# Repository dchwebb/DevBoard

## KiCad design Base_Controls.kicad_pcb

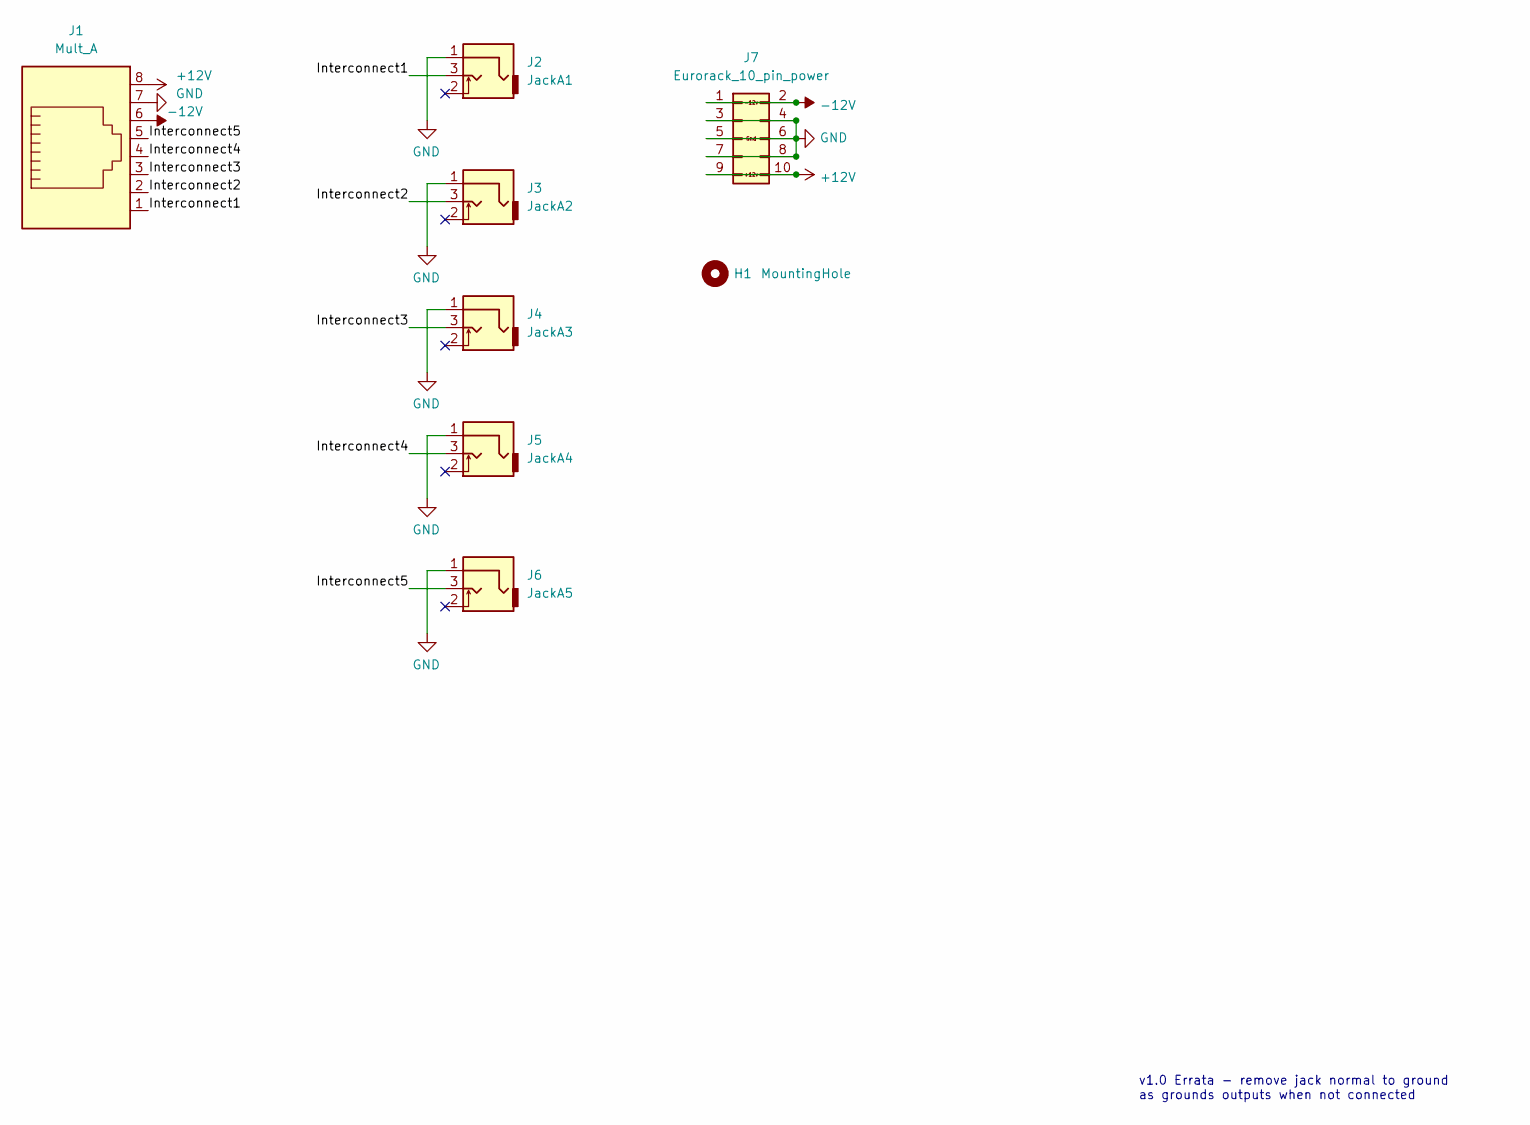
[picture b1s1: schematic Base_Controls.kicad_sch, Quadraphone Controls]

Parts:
H1: MountingHole; MountingHole_3.2mm_M3_ISO14580
J1: Mult_A; RJ45_Molex_42878-8506
J2: JackA1; THONKICONN_hole
J3: JackA2; THONKICONN_hole
J4: JackA3; THONKICONN_hole
J5: JackA4; THONKICONN_hole
J6: JackA5; THONKICONN_hole
J7: Eurorack_10_pin_power; PinHeader_2x05_P2.54mm_Vertical

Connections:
+12V: J1.8, J7.9, J7.10
-12V: J1.6, J7.1, J7.2
/Interconnect1: J1.1, J2.3
/Interconnect2: J1.2, J3.3
/Interconnect3: J1.3, J4.3
/Interconnect4: J1.4, J5.3
/Interconnect5: J1.5, J6.3
GND: J1.7, J2.1, J3.1, J4.1, J5.1, J6.1, J7.3, J7.4, J7.5, J7.6, J7.7, J7.8

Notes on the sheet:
v1.0 Errata - remove jack normal to ground as grounds outputs when not connected

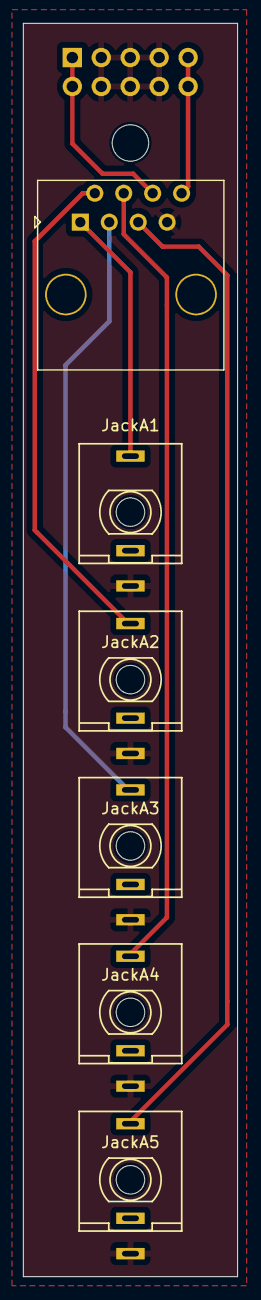
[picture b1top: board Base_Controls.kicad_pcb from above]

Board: 2 copper layers, 18.8 x 110.0 mm, 8 parts (1 on the bottom side), 8 nets.

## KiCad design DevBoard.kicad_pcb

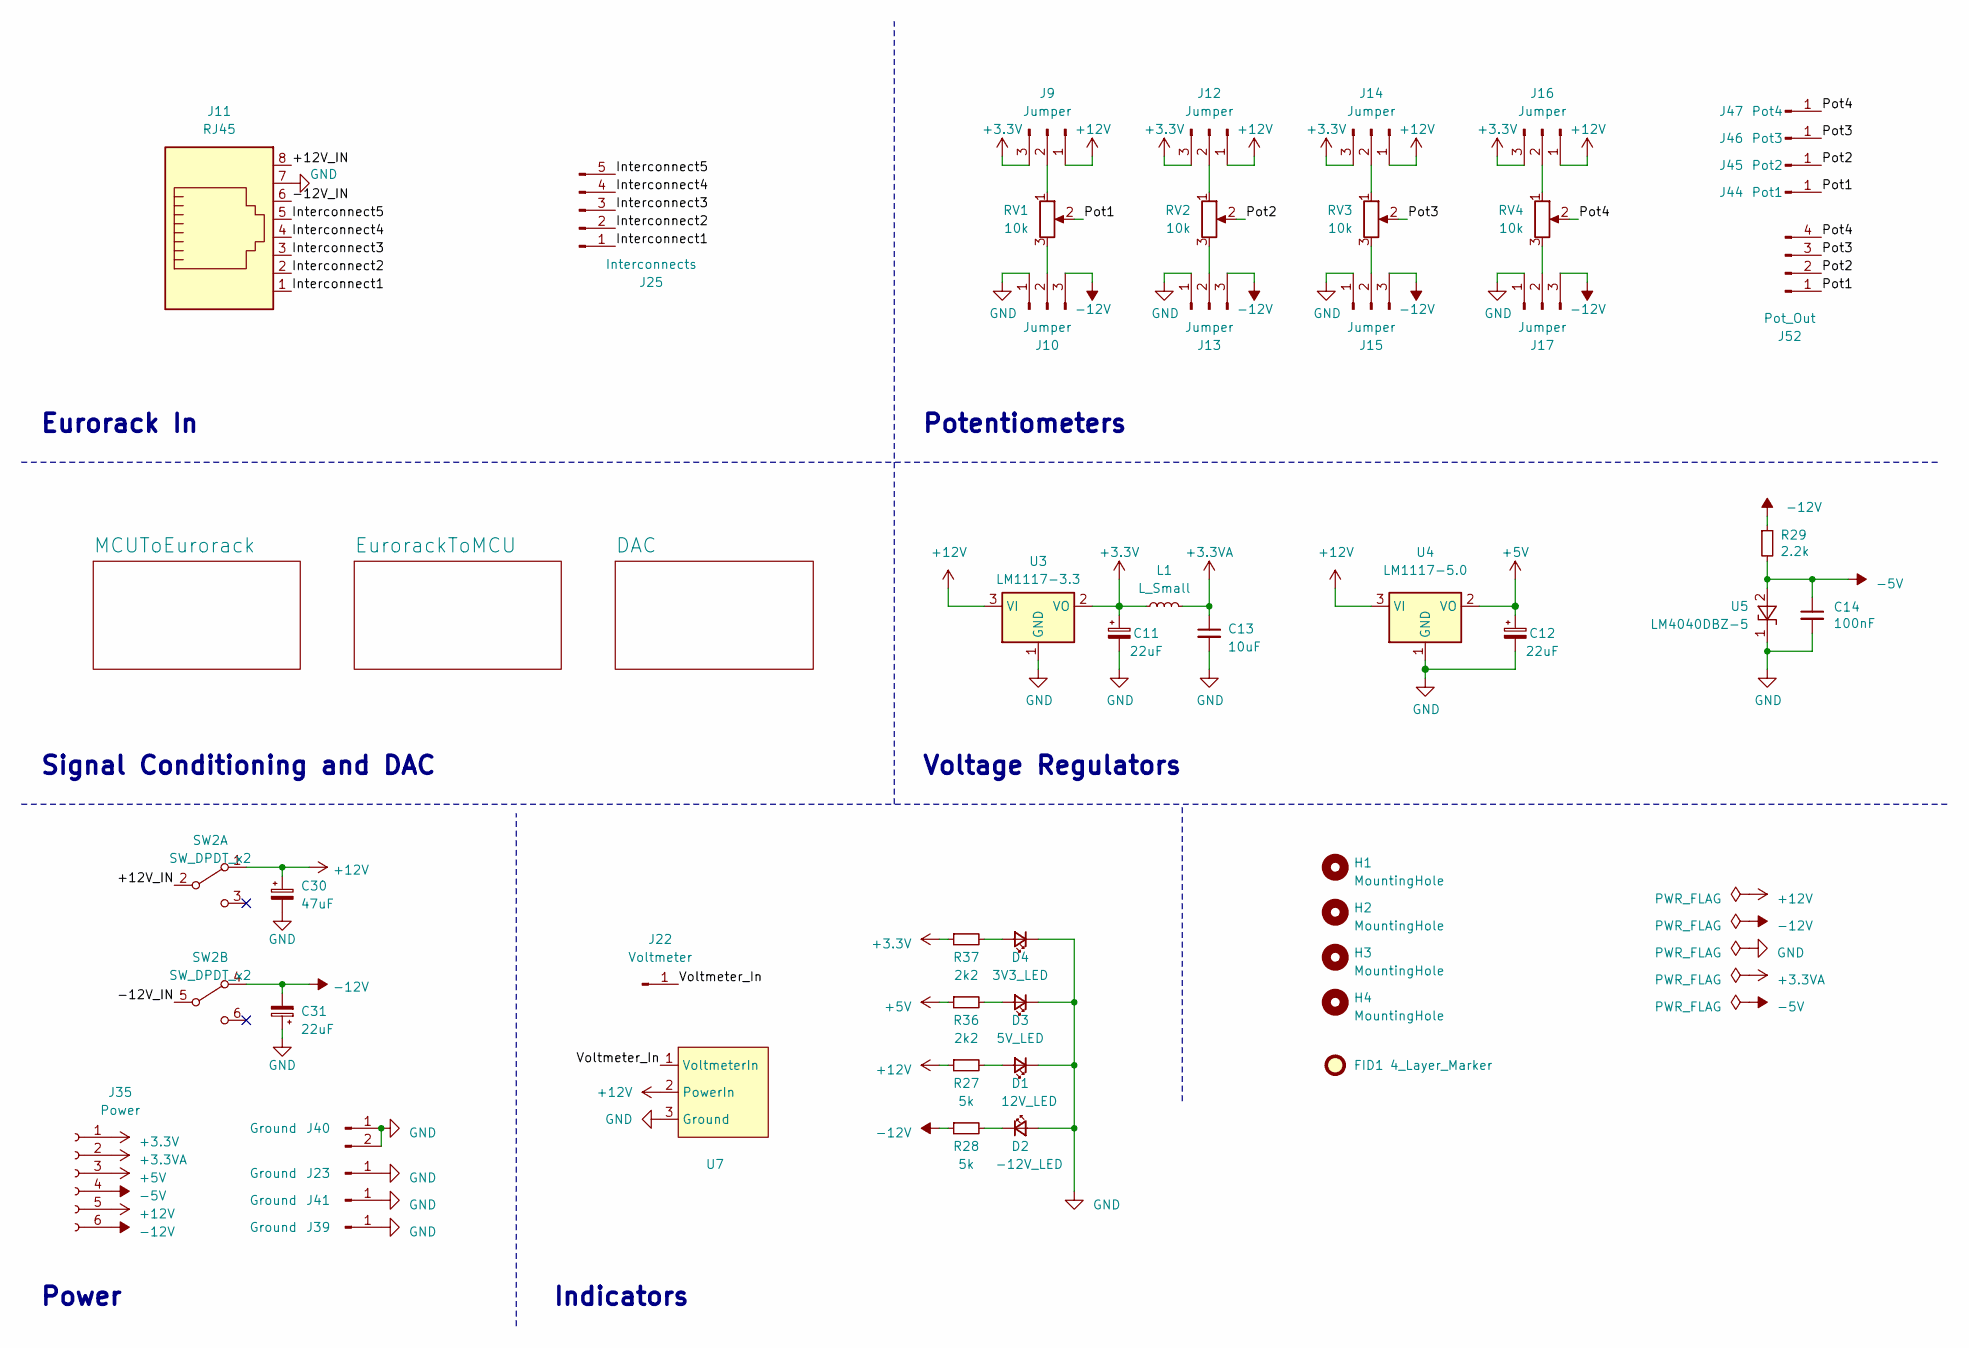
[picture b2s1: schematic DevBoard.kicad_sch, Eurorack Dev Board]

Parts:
C11, C12, C31: 22uF; CP_Elec_4x5.8
C13: 10uF; C_0805_2012Metric
C14: 100nF; C_0805_2012Metric
C30: 47uF; CP_Elec_5x5.4
D1: 12V_LED; LED_0603_1608Metric
D2: -12V_LED; LED_0603_1608Metric
D3: 5V_LED; LED_0603_1608Metric
D4: 3V3_LED; LED_0603_1608Metric
FID1: 4_Layer_Marker; 4_Layer_Markers
H1, H2, H3, H4: MountingHole; MountingHole_3.2mm_M3
J9, J10, J12, J13, J14, J15, J16, J17: Jumper; PinHeader_1x03_P2.54mm_Vertical
J11: RJ45; RJ45_Amphenol_Style
J22: Voltmeter; PinSocket_1x01_P2.54mm_Vertical
J23, J39, J41: Ground; PinHeader_1x01_P2.54mm_Vertical
J25: Interconnects; PinSocket_1x05_P2.54mm_Vertical
J35: Power; PinSocket_1x06_P2.54mm_Vertical
J40: Ground; PinSocket_1x02_P2.54mm_Vertical
J44: Pot1; PinHeader_1x01_P2.54mm_Vertical
J45: Pot2; PinHeader_1x01_P2.54mm_Vertical
J46: Pot3; PinHeader_1x01_P2.54mm_Vertical
J47: Pot4; PinHeader_1x01_P2.54mm_Vertical
J52: Pot_Out; PinSocket_1x04_P2.54mm_Vertical
L1: L_Small; L_0805_2012Metric_Pad1.05x1.20mm_HandSolder; Part_Number C1046
R27, R28: 5k; R_0805_2012Metric
R29: 2.2k; R_0805_2012Metric
R36, R37: 2k2; R_0805_2012Metric
RV1, RV2, RV3, RV4: 10k; Alpha_9mm_Potentiometer_Aligned
SW2: SW_DPDT_x2; 100DP6T1B1M2QE_ON_ON_ON
U3: LM1117-3.3; SOT-223-3_TabPin2
U4: LM1117-5.0; SOT-223-3_TabPin2
U5: LM4040DBZ-5; SOT-23
U7: MiniVoltmeter

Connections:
+3.3V: C11.1, J9.3, J12.3, J14.3, J16.3, J35.1, L1.1, R37.1, U3.2 (VO); also elsewhere on the board
+3.3VA: C13.1, J35.2, L1.2; also elsewhere on the board
+5V: C12.1, J35.3, R36.1, U4.2 (VO)
+12V: C30.1, J9.1, J12.1, J14.1, J16.1, J35.5, R27.1, SW2.1 (A), U3.3 (VI), U4.3 (VI), U7.2 (PowerIn); also elsewhere on the board
-5V: C14.1, J35.4, R29.2, U5.2 (A); also elsewhere on the board
-12V: C31.2, J10.3, J13.3, J15.3, J17.3, J35.6, R28.1, R29.1, SW2.4 (A); also elsewhere on the board
/+12V_IN: J11.8, SW2.2 (B)
/-12V_IN: J11.6, SW2.5 (B)
/Interconnect1: J11.1, J25.1
/Interconnect2: J11.2, J25.2
/Interconnect3: J11.3, J25.3
/Interconnect4: J11.4, J25.4
/Interconnect5: J11.5, J25.5
/Pot1: J44.1, J52.1, RV1.2
/Pot2: J45.1, J52.2, RV2.2
/Pot3: J46.1, J52.3, RV3.2
/Pot4: J47.1, J52.4, RV4.2
/Voltmeter_In: J22.1, U7.1 (VoltmeterIn)
GND: C11.2, C12.2, C13.2, C14.2, C30.2, C31.1, D1.1 (K), D2.2 (A), D3.1 (K), D4.1 (K), J10.1, J11.7, J13.1, J15.1, J17.1, J23.1, J39.1, J40.1, J40.2, J41.1, U3.1 (GND), U4.1 (GND), U5.1 (K), U7.3 (Ground); also elsewhere on the board
unnamed: D1.2 (A), R27.2
unnamed: D2.1 (K), R28.2
unnamed: D3.2 (A), R36.2
unnamed: D4.2 (A), R37.2
unnamed: J9.2, RV1.1
unnamed: J10.2, RV1.3
unnamed: J12.2, RV2.1
unnamed: J13.2, RV2.3
unnamed: J14.2, RV3.1
unnamed: J15.2, RV3.3
unnamed: J16.2, RV4.1
unnamed: J17.2, RV4.3

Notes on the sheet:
Eurorack In
Potentiometers
Indicators
Power
Voltage Regulators
Signal Conditioning and DAC

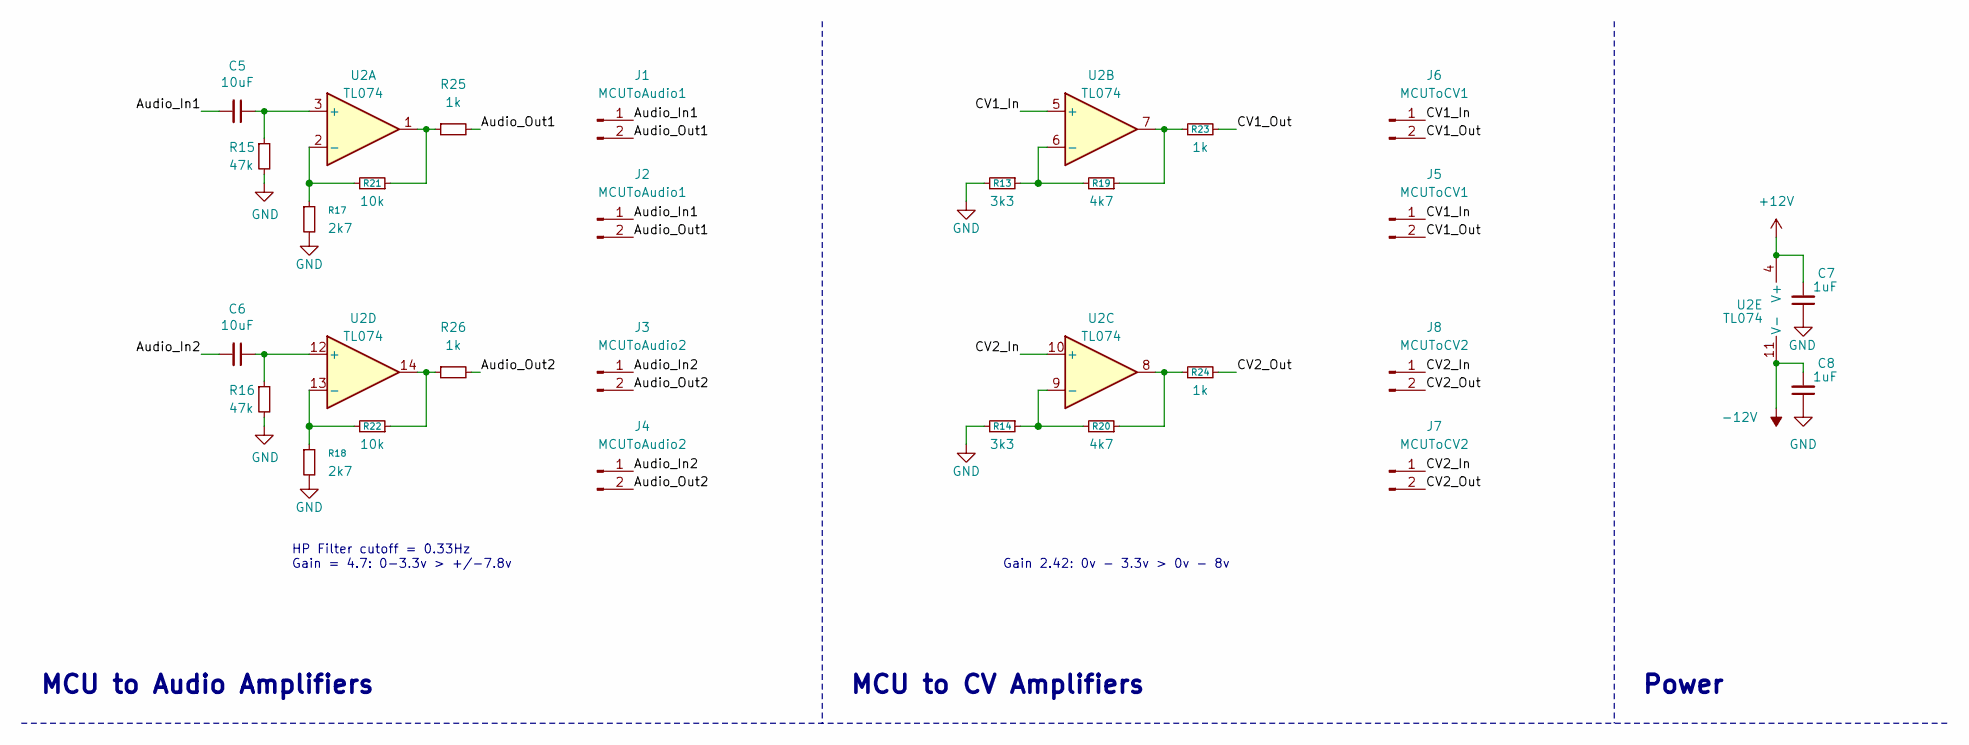
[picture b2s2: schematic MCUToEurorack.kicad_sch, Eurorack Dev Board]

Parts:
C5, C6: 10uF; C_0805_2012Metric
C7, C8: 1uF; C_0805_2012Metric
J1: MCUToAudio1; PinSocket_1x02_P2.54mm_Vertical
J2: MCUToAudio1; PinHeader_1x02_P2.54mm_Vertical
J3: MCUToAudio2; PinSocket_1x02_P2.54mm_Vertical
J4: MCUToAudio2; PinHeader_1x02_P2.54mm_Vertical
J5: MCUToCV1; PinHeader_1x02_P2.54mm_Vertical
J6: MCUToCV1; PinSocket_1x02_P2.54mm_Vertical
J7: MCUToCV2; PinHeader_1x02_P2.54mm_Vertical
J8: MCUToCV2; PinSocket_1x02_P2.54mm_Vertical
R13, R14: 3k3; R_0805_2012Metric; Part_Number C22978
R15, R16: 47k; R_0805_2012Metric
R17, R18: 2k7; R_0805_2012Metric; Part_Number C22978
R19, R20: 4k7; R_0805_2012Metric; Part_Number C23162
R21, R22: 10k; R_0805_2012Metric; Part_Number C23162
R23, R24: 1k; R_0805_2012Metric; Part_Number C21190
R25, R26: 1k; R_0805_2012Metric
U2: TL074; SOIC-14_3.9x8.7mm_P1.27mm

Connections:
+12V: C7.2, U2.4 (V+); also elsewhere on the board
-12V: C8.2, U2.11 (V-); also elsewhere on the board
/MCUToEurorack/Audio_In1: C5.2, J1.1, J2.1
/MCUToEurorack/Audio_In2: C6.2, J3.1, J4.1
/MCUToEurorack/Audio_Out1: J1.2, J2.2, R25.2
/MCUToEurorack/Audio_Out2: J3.2, J4.2, R26.2
/MCUToEurorack/CV1_In: J5.1, J6.1, U2.5 (+)
/MCUToEurorack/CV1_Out: J5.2, J6.2, R23.2
/MCUToEurorack/CV2_In: J7.1, J8.1, U2.10 (+)
/MCUToEurorack/CV2_Out: J7.2, J8.2, R24.2
GND: C7.1, C8.1, R13.2, R14.2, R15.2, R16.2, R17.2, R18.2; also elsewhere on the board
unnamed: R19.1, R23.1, U2.7
unnamed: R20.1, R24.1, U2.8
unnamed: R21.1, R25.1, U2.1
unnamed: R22.1, R26.1, U2.14
unnamed: C5.1, R15.1, U2.3 (+)
unnamed: R17.1, R21.2, U2.2 (-)
unnamed: R13.1, R19.2, U2.6 (-)
unnamed: R14.1, R20.2, U2.9 (-)
unnamed: C6.1, R16.1, U2.12 (+)
unnamed: R18.1, R22.2, U2.13 (-)

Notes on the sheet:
HP Filter cutoff = 0.33Hz Gain = 4.7: 0-3.3v > +/-7.8v
MCU to Audio Amplifiers
MCU to CV Amplifiers
Gain 2.42: 0v - 3.3v > 0v - 8v
Power

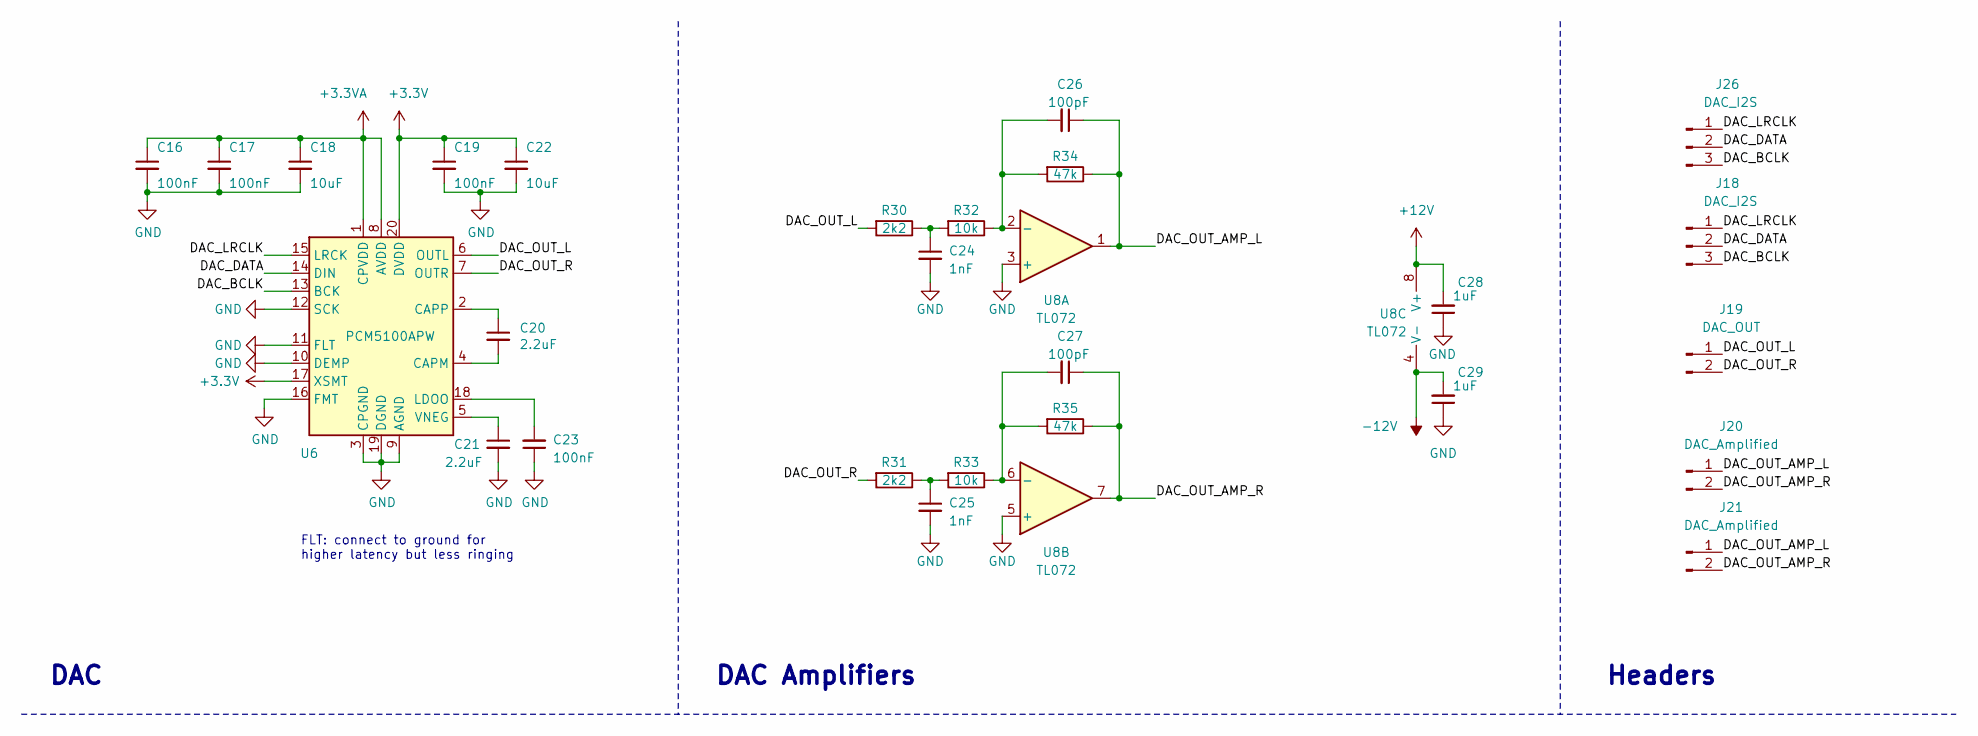
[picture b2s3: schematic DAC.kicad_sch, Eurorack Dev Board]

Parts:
C16, C17, C19, C23: 100nF; C_0805_2012Metric; Part_Number C14663
C18, C22: 10uF; C_0805_2012Metric; Part_Number C15850
C20, C21: 2.2uF; C_0805_2012Metric; Part_Number C23630
C24, C25: 1nF; C_0805_2012Metric; Part_Number C1588
C26, C27: 100pF; C_0805_2012Metric; Part_Number C14858
C28, C29: 1uF; C_0805_2012Metric
J18: DAC_I2S; PinHeader_1x03_P2.54mm_Vertical
J19: DAC_OUT; PinHeader_1x02_P2.54mm_Vertical
J20: DAC_Amplified; PinSocket_1x02_P2.54mm_Vertical
J21: DAC_Amplified; PinHeader_1x02_P2.54mm_Vertical
J26: DAC_I2S; PinSocket_1x03_P2.54mm_Vertical
R30, R31: 2k2; R_0805_2012Metric; Part_Number C4190
R32, R33: 10k; R_0805_2012Metric; Part_Number C25804
R34, R35: 47k; R_0805_2012Metric; Part_Number C25819
U6: PCM5100APW; TSSOP-20_4.4x6.5mm_P0.65mm; Part_Number C131154
U8: TL072; SOIC-8_3.9x4.9mm_P1.27mm; Part_Number C6961

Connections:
+3.3V: C19.1, C22.1, U6.17 (XSMT), U6.20 (DVDD); also elsewhere on the board
+3.3VA: C16.1, C17.1, C18.1, U6.1 (CPVDD), U6.8 (AVDD); also elsewhere on the board
+12V: C28.2, U8.8 (V+); also elsewhere on the board
-12V: C29.2, U8.4 (V-); also elsewhere on the board
/DAC/DAC_BCLK: J18.3, J26.3, U6.13 (BCK)
/DAC/DAC_DATA: J18.2, J26.2, U6.14 (DIN)
/DAC/DAC_LRCLK: J18.1, J26.1, U6.15 (LRCK)
/DAC/DAC_OUT_AMP_L: C26.1, J20.1, J21.1, R34.1, U8.1
/DAC/DAC_OUT_AMP_R: C27.1, J20.2, J21.2, R35.1, U8.7
/DAC/DAC_OUT_L: J19.1, R30.2, U6.6 (OUTL)
/DAC/DAC_OUT_R: J19.2, R31.2, U6.7 (OUTR)
GND: C16.2, C17.2, C18.2, C19.2, C21.2, C22.2, C23.1, C24.2, C25.2, C28.1, C29.1, U6.3 (CPGND), U6.9 (AGND), U6.10 (DEMP), U6.11 (FLT), U6.12 (SCK), U6.16 (FMT), U6.19 (DGND), U8.3 (+), U8.5 (+); also elsewhere on the board
unnamed: C24.1, R30.1, R32.2
unnamed: C25.1, R31.1, R33.2
unnamed: C20.2, U6.4 (CAPM)
unnamed: C20.1, U6.2 (CAPP)
unnamed: C23.2, U6.18 (LDOO)
unnamed: C21.1, U6.5 (VNEG)
unnamed: C26.2, R32.1, R34.2, U8.2 (-)
unnamed: C27.2, R33.1, R35.2, U8.6 (-)

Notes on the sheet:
Headers
DAC Amplifiers
DAC
FLT: connect to ground for higher latency but less ringing

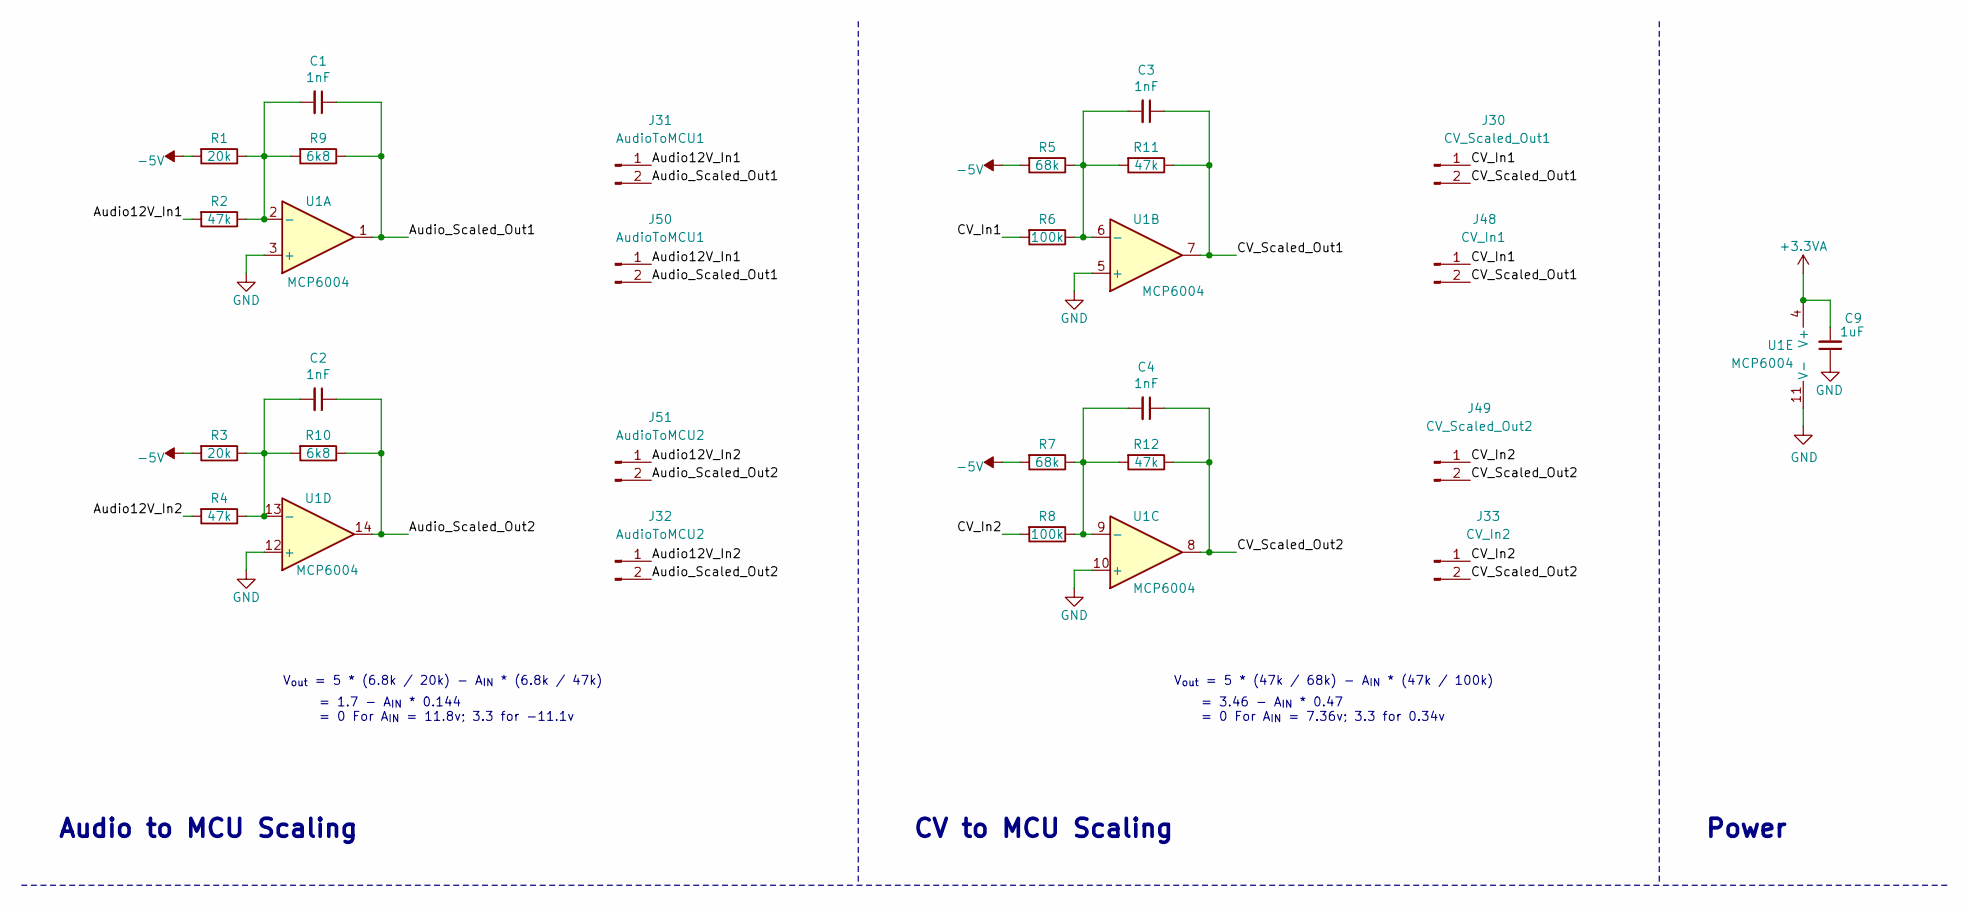
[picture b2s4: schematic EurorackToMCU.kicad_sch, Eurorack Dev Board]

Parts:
C1, C2, C3, C4: 1nF; C_0805_2012Metric; Part_Number C1595
C9: 1uF; C_0805_2012Metric
J30: CV_Scaled_Out1; PinSocket_1x02_P2.54mm_Vertical
J31: AudioToMCU1; PinSocket_1x02_P2.54mm_Vertical
J32: AudioToMCU2; PinHeader_1x02_P2.54mm_Vertical
J33: CV_In2; PinHeader_1x02_P2.54mm_Vertical
J48: CV_In1; PinHeader_1x02_P2.54mm_Vertical
J49: CV_Scaled_Out2; PinSocket_1x02_P2.54mm_Vertical
J50: AudioToMCU1; PinHeader_1x02_P2.54mm_Vertical
J51: AudioToMCU2; PinSocket_1x02_P2.54mm_Vertical
R1, R3: 20k; R_0805_2012Metric; Part_Number C4184
R2, R4, R11, R12: 47k; R_0805_2012Metric; Part_Number C25819
R5, R7: 68k; R_0805_2012Metric; Part_Number C23231
R6, R8: 100k; R_0805_2012Metric; Part_Number C25803
R9, R10: 6k8; R_0805_2012Metric; Part_Number C23212
U1: MCP6004; SOIC-14_3.9x8.7mm_P1.27mm; Part_Number C116668

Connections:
+3.3VA: C9.2, U1.4 (V+); also elsewhere on the board
-5V: R1.2, R3.2, R5.2, R7.2; also elsewhere on the board
/EurorackToMCU/Audio12V_In1: J31.1, J50.1, R2.2
/EurorackToMCU/Audio12V_In2: J32.1, J51.1, R4.2
/EurorackToMCU/Audio_Scaled_Out1: C1.1, J31.2, J50.2, R9.1, U1.1
/EurorackToMCU/Audio_Scaled_Out2: C2.1, J32.2, J51.2, R10.1, U1.14
/EurorackToMCU/CV_In1: J30.1, J48.1, R6.2
/EurorackToMCU/CV_In2: J33.1, J49.1, R8.2
/EurorackToMCU/CV_Scaled_Out1: C3.1, J30.2, J48.2, R11.1, U1.7
/EurorackToMCU/CV_Scaled_Out2: C4.1, J33.2, J49.2, R12.1, U1.8
GND: C9.1, U1.3 (+), U1.5 (+), U1.10 (+), U1.11 (V-), U1.12 (+); also elsewhere on the board
unnamed: C1.2, R1.1, R2.1, R9.2, U1.2 (-)
unnamed: C3.2, R5.1, R6.1, R11.2, U1.6 (-)
unnamed: C4.2, R7.1, R8.1, R12.2, U1.9 (-)
unnamed: C2.2, R3.1, R4.1, R10.2, U1.13 (-)

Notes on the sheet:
Power
Audio to MCU Scaling
CV to MCU Scaling
V_{out} = 5 * (6.8k / 20k) - A_{IN} * (6.8k / 47k)
V_{out} = 5 * (47k / 68k) - A_{IN} * (47k / 100k)
= 3.46 - A_{IN} * 0.47 = 0 For A_{IN} = 7.36v; 3.3 for 0.34v
= 1.7 - A_{IN} * 0.144 = 0 For A_{IN} = 11.8v; 3.3 for -11.1v

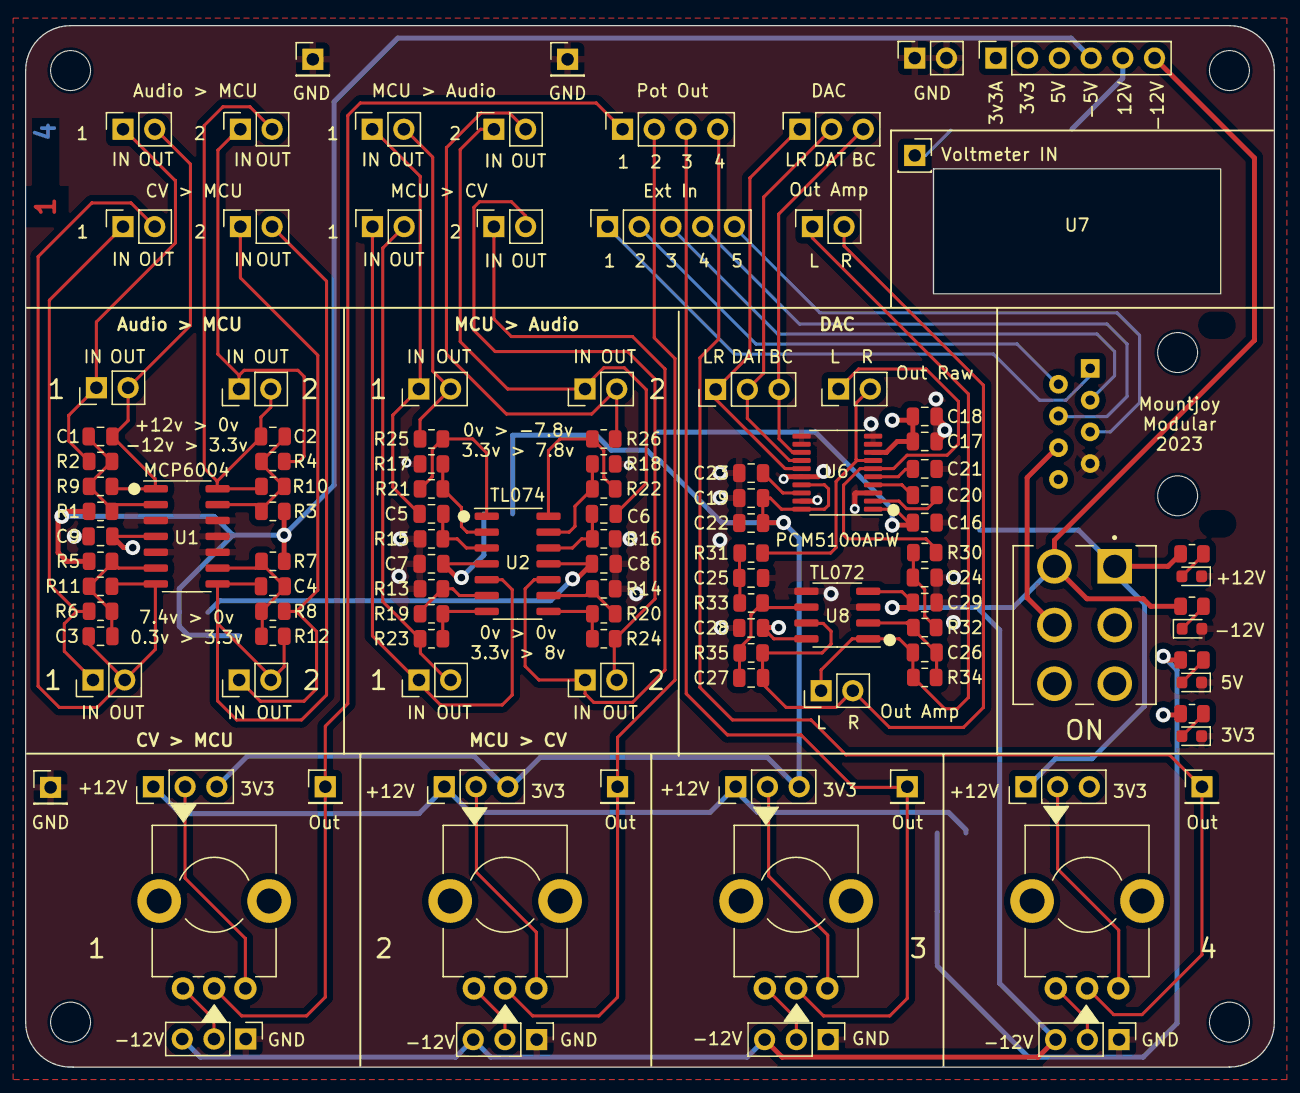
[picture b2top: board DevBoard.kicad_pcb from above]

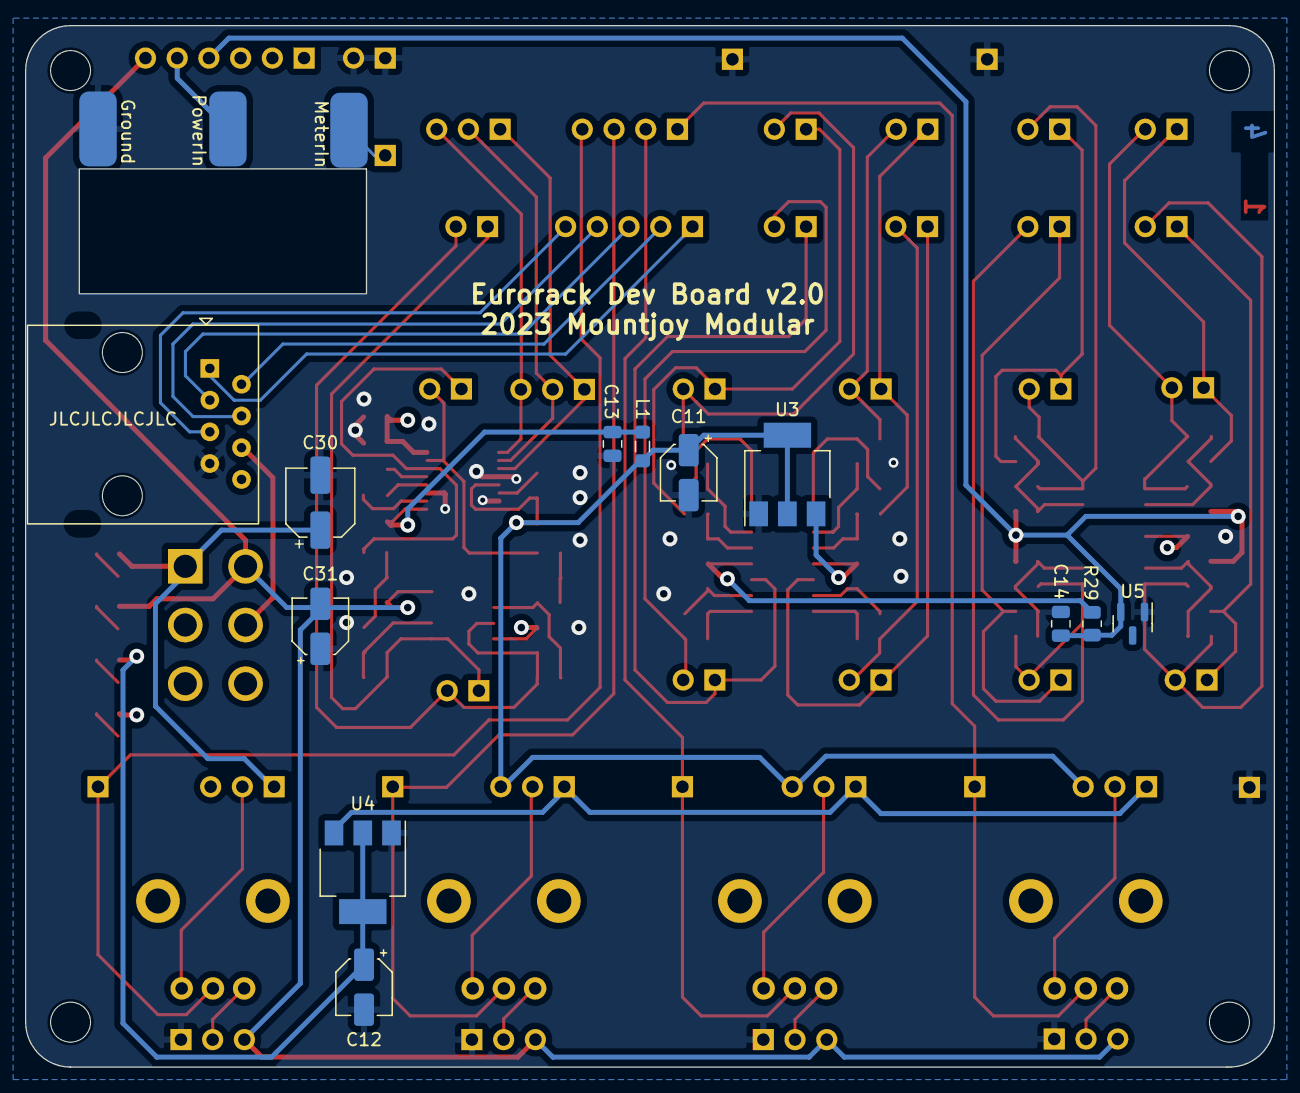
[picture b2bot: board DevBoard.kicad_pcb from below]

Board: 4 copper layers, 100.0 x 83.4 mm, 131 parts (12 on the bottom side), 76 nets.

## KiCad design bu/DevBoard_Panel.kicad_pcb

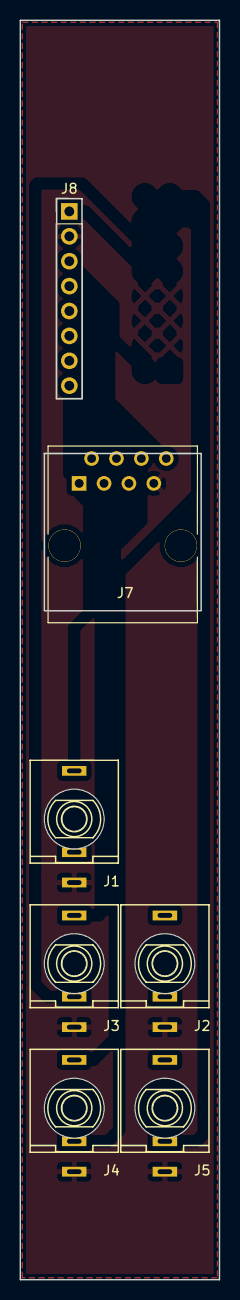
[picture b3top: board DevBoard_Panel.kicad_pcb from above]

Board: 2 copper layers, 20.3 x 128.5 mm, 7 parts (0 on the bottom side), 8 nets, no tracks yet.

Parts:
J1, J2, J3, J4, J5: AudioJack2_Ground_Switch; THONKICONN_hole
J7: RJ45; RJ45_8
J8: Conn_01x08_Female; Pin_Header_Straight_1x08_Pitch2.54mm

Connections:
+12V: J7.3, J8.1
-12V: J7.5, J8.3
GND: J1.1, J2.1, J3.1, J4.1, J5.1, J7.7, J8.2
Jack1: J1.3, J7.1, J8.8
Jack2: J2.3, J7.2, J8.7
Jack3: J3.3, J7.4, J8.6
Jack4: J4.3, J7.6, J8.5
Jack5: J5.3, J7.8, J8.4

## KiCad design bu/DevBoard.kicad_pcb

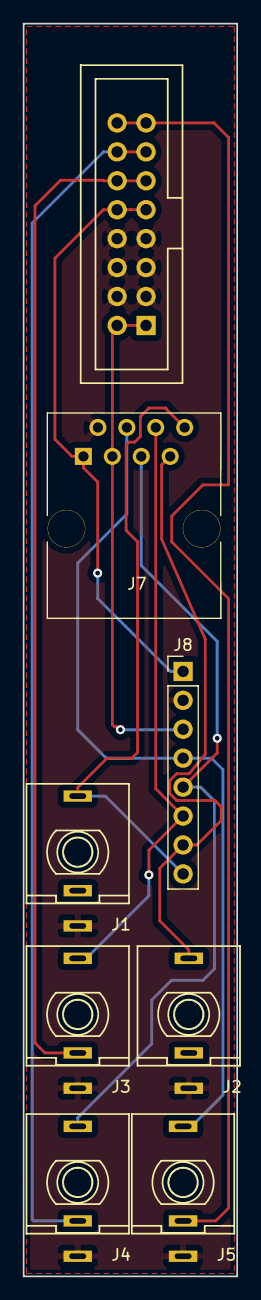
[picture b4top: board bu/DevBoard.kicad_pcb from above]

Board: 2 copper layers, 18.8 x 110.0 mm, 8 parts (0 on the bottom side), 11 nets.

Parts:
J1, J2, J3, J4, J5: AudioJack2_Ground_Switch; THONKICONN_hole
J6: Eurorack_16_pin_power; Eurorack_16_pin_header
J7: RJ45; RJ45_8
J8: Conn_01x08_Female; Pin_Header_Straight_1x08_Pitch2.54mm

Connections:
+5V: J3.2, J6.11, J6.12
+12V: J6.9, J6.10, J7.1, J8.1
-12V: J6.1, J6.2, J7.3, J8.3
CV: J4.2, J6.13, J6.14
GND: J1.1, J2.1, J3.1, J4.1, J5.1, J6.3, J6.4, J6.5, J6.6, J6.7, J6.8, J7.2, J8.2
Gate: J5.2, J6.15, J6.16
Jack1: J1.3, J7.8, J8.8
Jack2: J2.3, J7.7, J8.7
Jack3: J3.3, J7.6, J8.6
Jack4: J4.3, J7.5, J8.5
Jack5: J5.3, J7.4, J8.4

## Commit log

2023-03-12 Started mark 2 Dev Board
2023-03-25 First draft of schematic done; started laying out PCB
2023-03-25 Started PCB layout
2023-03-27 Routing scaling circuits
2023-03-27 Further layout
2023-03-28 PCB Updates
2023-03-28 First draft routing completed
2023-03-28 Cleaned up schematic
2023-03-29 Layout tweaks
2023-03-30 Preparing for production
2023-04-16 Updated net classes
2023-08-18 Fixed normal to ground of base unit jacks
